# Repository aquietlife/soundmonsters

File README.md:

# Sound Monsters

[Board Layout](https://github.com/aquietlife/soundmonsters/raw/master/soundmonsters_board_layout.pdf)

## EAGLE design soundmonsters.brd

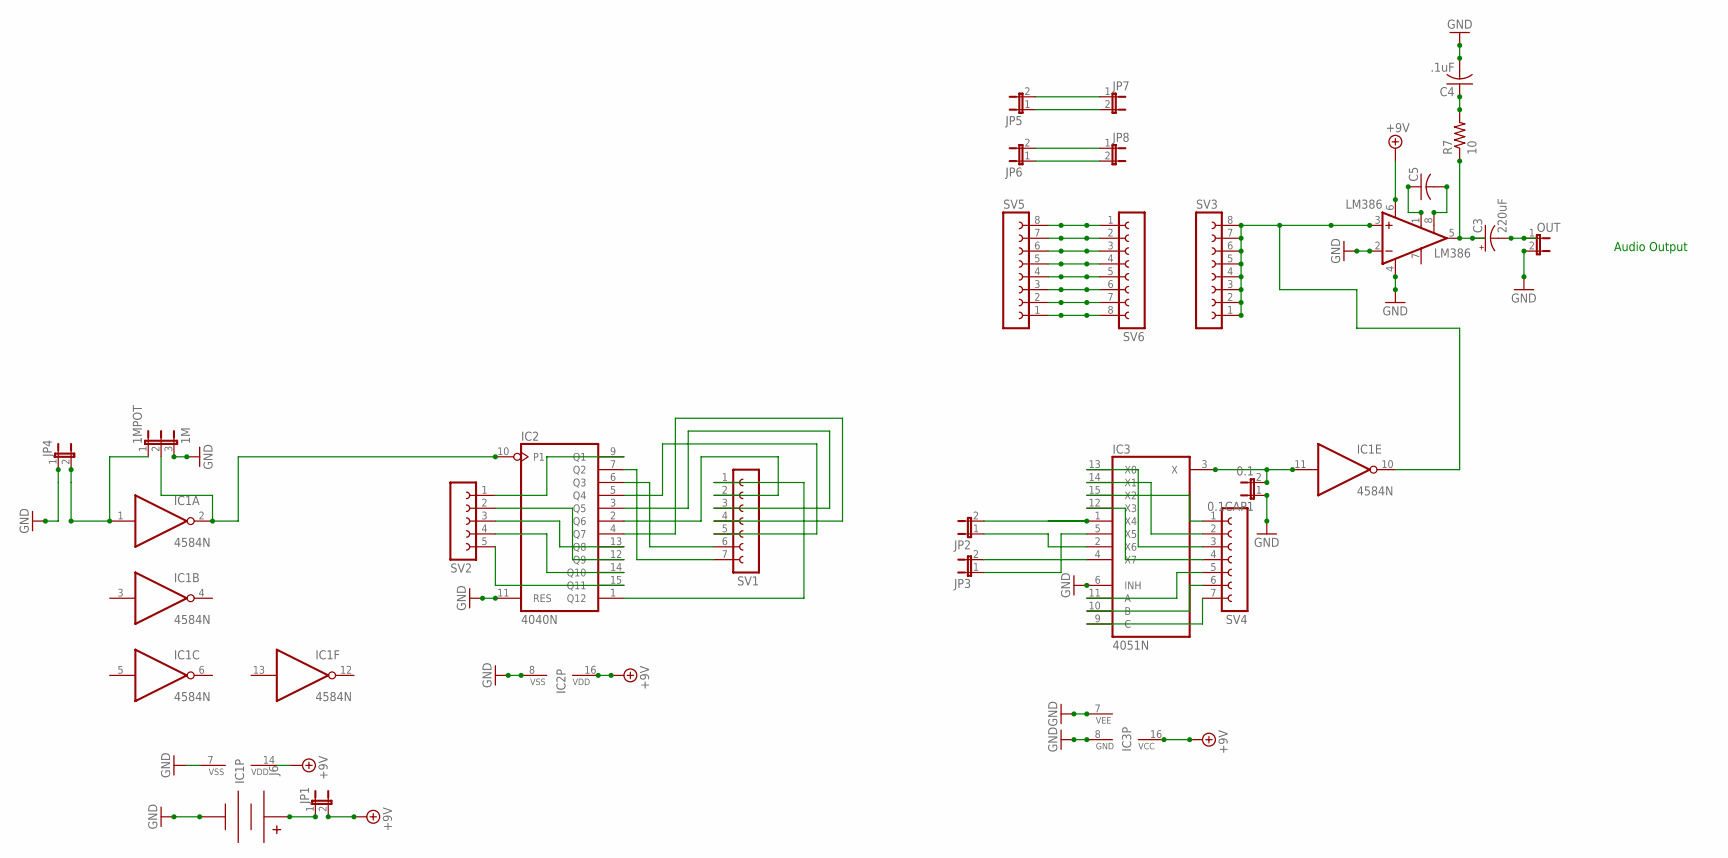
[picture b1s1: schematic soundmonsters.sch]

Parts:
0.1CAP1: 0.1; JP1
1MPOT: 1M; JP2
C3: 220uF; E3,5-8
C4: .1uF; C025-024X044
C5: C-US025-024X044; C025-024X044
IC1: 4584N; DIL14
IC2: 4040N; DIL16
IC3: 4051N; DIL16
J6: BC9VPC
JP1, JP2, JP3, JP4, JP5, JP6, JP7, JP8: JP1E; JP1
LM386: LM386; DIL08
OUT: JP1E; JP1
R7: 10; 0204/7
SV1, SV4: FE07-1; FE07
SV2: FE05-1
SV3, SV5, SV6: FE08-1; FE08

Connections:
+9V: IC1.14 (VDD), IC2.16 (VDD), IC3.16 (VCC), JP1.2, LM386.6 (VS)
GND: 0.1CAP1.1, 1MPOT.3, C4.2, IC1.7 (VSS), IC2.8 (VSS), IC2.11 (RES), IC3.6 (INH), IC3.7 (VEE), IC3.8 (GND), J6.V-, JP4.1, LM386.2 (-IN), LM386.4 (GND), OUT.2
unnamed: 1MPOT.1, IC1.1 (I), JP4.2
unnamed: 1MPOT.2, IC1.2 (O), IC2.10 (P1)
unnamed: IC3.1 (X4), JP2.2
unnamed: 0.1CAP1.2, IC1.11 (I), IC3.3 (X)
unnamed: C5.1, LM386.1 (GAIN)
unnamed: IC2.1 (Q12), SV1.1
unnamed: IC2.2 (Q6), SV1.2
unnamed: IC2.3 (Q5), SV1.3
unnamed: IC2.4 (Q7), SV1.4
unnamed: C3.+, LM386.5 (OUT), R7.1
unnamed: C3.-, OUT.1
unnamed: IC2.5 (Q4), SV1.5
unnamed: C4.1, R7.2
unnamed: C5.2, LM386.8 (GAIN)
unnamed: IC2.6 (Q3), SV1.6
unnamed: IC2.7 (Q2), SV1.7
unnamed: IC2.9 (Q1), SV2.1
unnamed: IC2.12 (Q9), SV2.2
unnamed: IC2.13 (Q8), SV2.3
unnamed: IC2.14 (Q10), SV2.4
unnamed: IC2.15 (Q11), SV2.5
unnamed: IC3.2 (X6), JP2.1
unnamed: IC3.4 (X7), JP3.2
unnamed: IC3.5 (X5), JP3.1
unnamed: IC3.9 (C), SV4.7
unnamed: IC3.10 (B), SV4.6
unnamed: IC3.11 (A), SV4.5
unnamed: IC3.12 (X3), SV4.4
unnamed: IC3.13 (X0), SV4.3
unnamed: IC3.14 (X1), SV4.2
unnamed: IC3.15 (X2), SV4.1
unnamed: SV5.8, SV6.1
unnamed: SV5.7, SV6.2
unnamed: SV5.6, SV6.3
unnamed: SV5.5, SV6.4
unnamed: SV5.4, SV6.5
unnamed: SV5.3, SV6.6
unnamed: SV5.2, SV6.7
unnamed: SV5.1, SV6.8
unnamed: JP5.2, JP7.1
unnamed: IC1.10 (O), LM386.3 (+IN), SV3.1, SV3.2, SV3.3, SV3.4, SV3.5, SV3.6, SV3.7, SV3.8
unnamed: JP5.1, JP7.2
unnamed: JP6.2, JP8.1
unnamed: JP6.1, JP8.2
unnamed: J6.V+, JP1.1

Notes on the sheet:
Audio Output

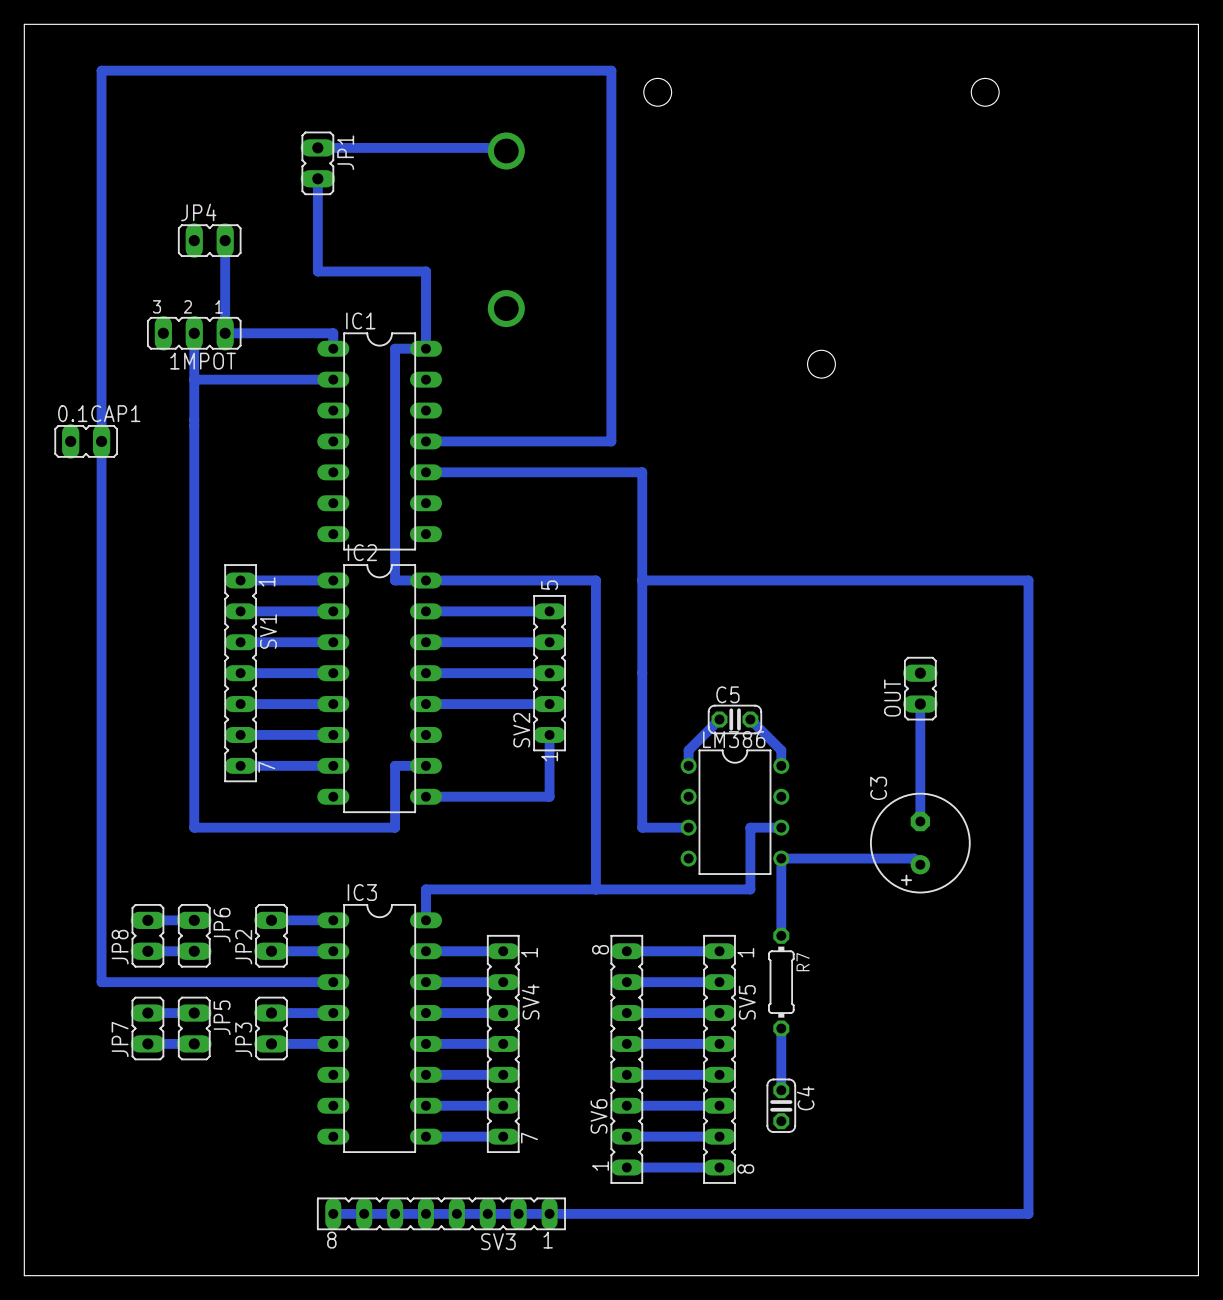
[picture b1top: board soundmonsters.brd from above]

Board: 2 copper layers, 96.5 x 102.9 mm, 26 parts (1 on the bottom side), 47 nets.

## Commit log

2018-08-04 added readme and board layout
2018-08-04 added link to layout

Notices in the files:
parts and their libraries:
SparkFun-Connectors: Licensing: Creative Commons ShareAlike 4.0 International - https://creativecommons.org/licenses/by-sa/4.0
